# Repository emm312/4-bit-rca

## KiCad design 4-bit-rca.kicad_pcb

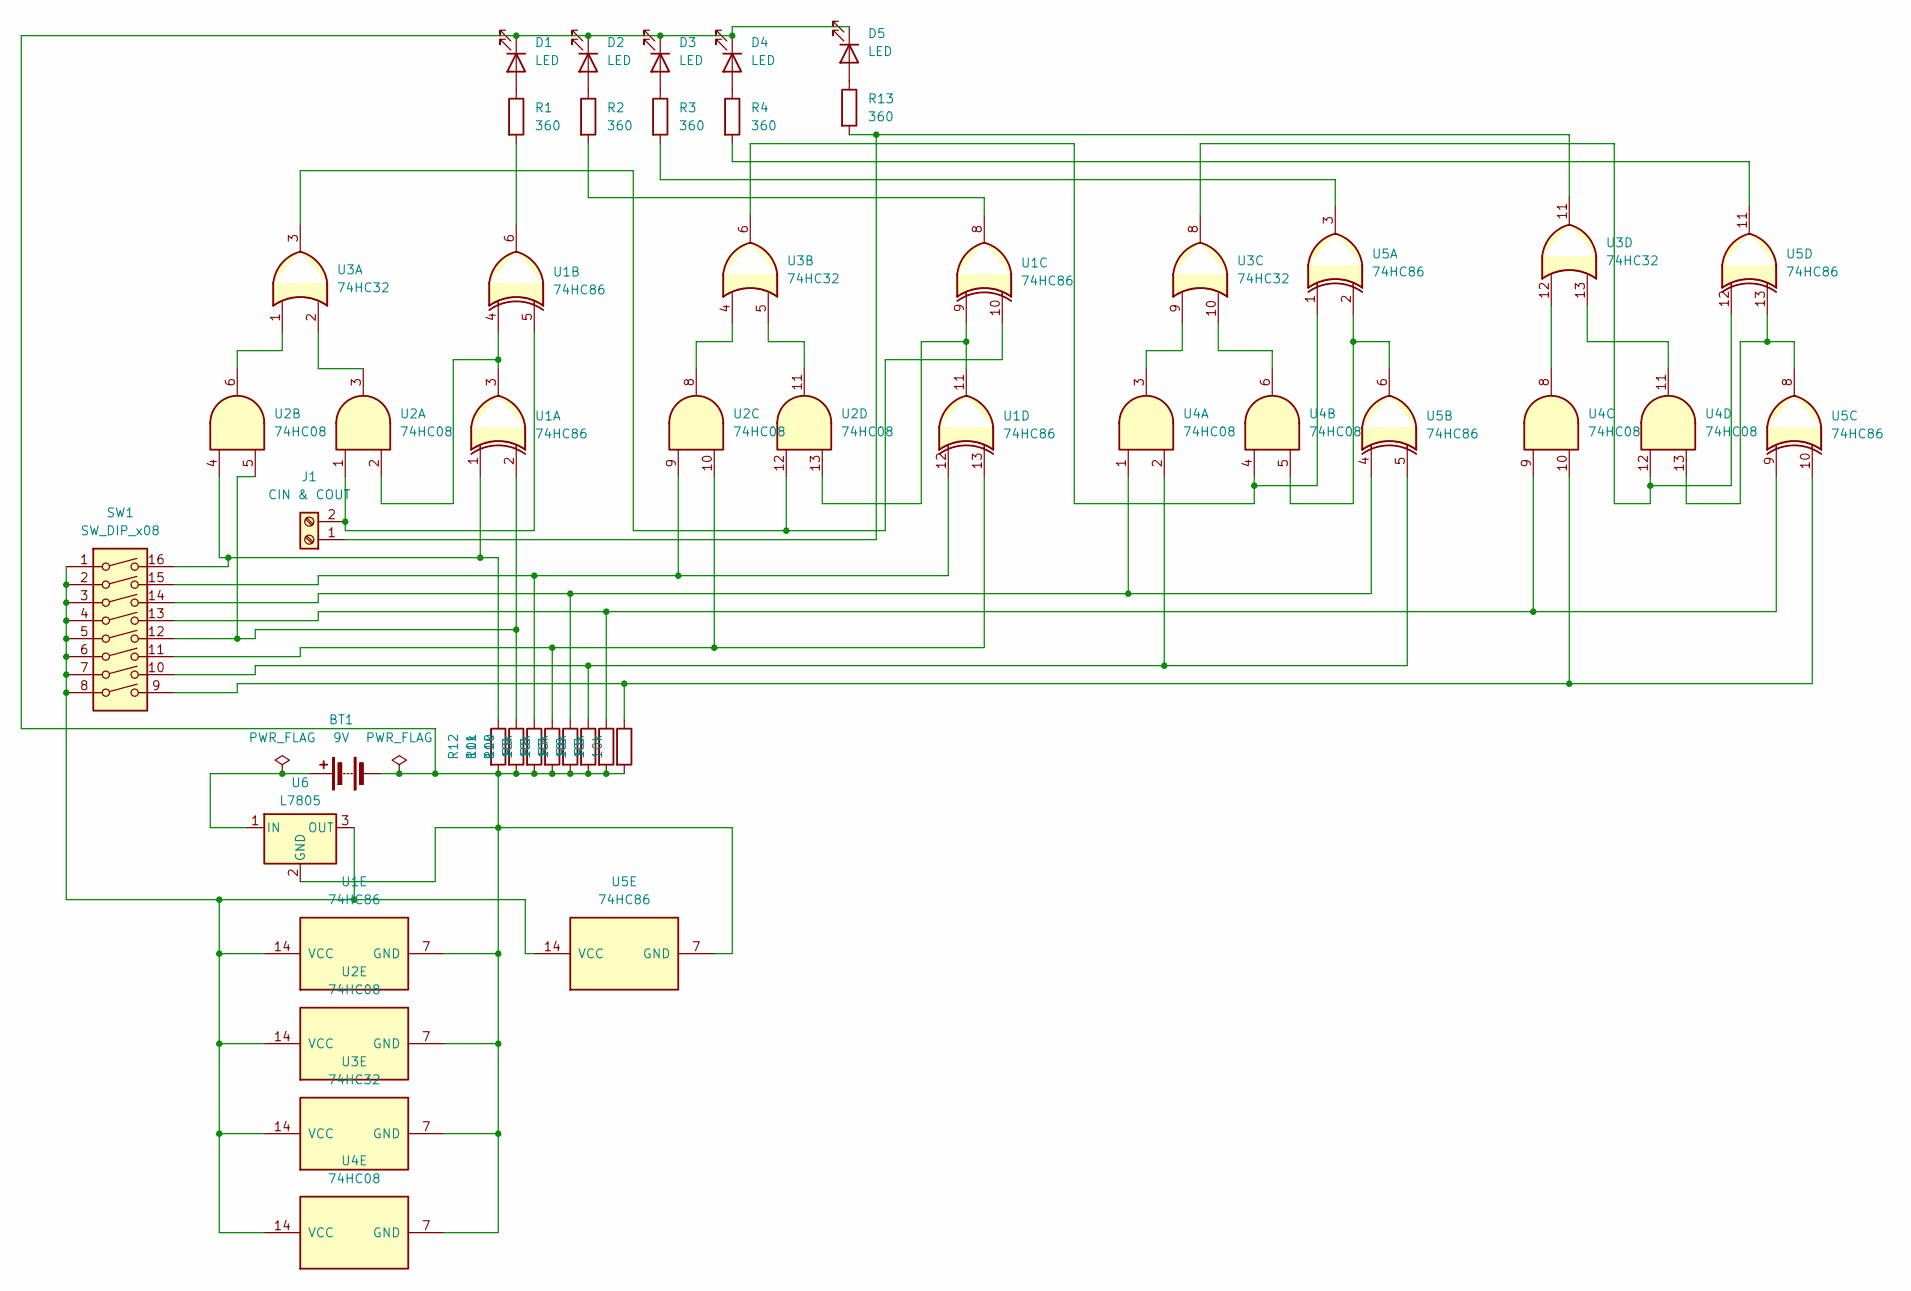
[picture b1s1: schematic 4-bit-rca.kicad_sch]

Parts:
BT1: 9V; PinHeader_1x02_P2.54mm_Vertical
D1, D2, D3, D4, D5: LED; LED_D5.0mm
J1: CIN & COUT; PinHeader_1x02_P2.54mm_Vertical
R1, R2, R3, R4, R13: 360; R_Axial_DIN0207_L6.3mm_D2.5mm_P10.16mm_Horizontal
R5, R6, R7, R8, R9, R10, R11, R12: 10k; R_Axial_DIN0207_L6.3mm_D2.5mm_P10.16mm_Horizontal
SW1: SW_DIP_x08; SW_DIP_SPSTx08_Slide_6.7x21.88mm_W7.62mm_P2.54mm_LowProfile
U1, U5: 74HC86; DIP-14_W7.62mm_Socket_LongPads
U2, U4: 74HC08; DIP-14_W7.62mm_Socket_LongPads
U3: 74HC32; DIP-14_W7.62mm_Socket_LongPads
U6: L7805; TO-220-3_Vertical

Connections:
unnamed: BT1.1 (+), U6.1 (IN)
unnamed: BT1.2 (-), D1.1 (K), D2.1 (K), D3.1 (K), D4.1 (K), D5.1 (K), R5.2, R6.2, R7.2, R8.2, R9.2, R10.2, R11.2, R12.2, U1.7 (GND), U2.7 (GND), U3.7 (GND), U4.7 (GND), U5.7 (GND), U6.2 (GND)
unnamed: D1.2 (A), R1.1
unnamed: D2.2 (A), R2.1
unnamed: D3.2 (A), R3.1
unnamed: D4.2 (A), R4.1
unnamed: D5.2 (A), R13.1
unnamed: J1.1, R13.2, U3.11
unnamed: J1.2, U1.5, U2.1
unnamed: R1.2, U1.6
unnamed: R2.2, U1.8
unnamed: R3.2, U5.3
unnamed: R4.2, U5.11
unnamed: R5.1, SW1.9, U4.10, U5.10
unnamed: R6.1, SW1.13, U4.9, U5.9
unnamed: R7.1, SW1.10, U4.2, U5.5
unnamed: R8.1, SW1.14, U4.1, U5.4
unnamed: R9.1, SW1.11, U1.13, U2.10
unnamed: R10.1, SW1.15, U1.12, U2.9
unnamed: R11.1, SW1.12, U1.2, U2.5
unnamed: R12.1, SW1.16, U1.1, U2.4
unnamed: U1.3, U1.4, U2.2
unnamed: U1.10, U2.12, U3.3
unnamed: U1.9, U1.11, U2.13
unnamed: SW1.1, SW1.2, SW1.3, SW1.4, SW1.5, SW1.6, SW1.7, SW1.8, U1.14 (VCC), U2.14 (VCC), U3.14 (VCC), U4.14 (VCC), U5.14 (VCC), U6.3 (OUT)
unnamed: U2.3, U3.2
unnamed: U2.6, U3.1
unnamed: U2.8, U3.4
unnamed: U2.11, U3.5
unnamed: U3.6, U4.4, U5.1
unnamed: U3.8, U4.12, U5.12
unnamed: U3.9, U4.3
unnamed: U3.10, U4.6
unnamed: U3.12, U4.8
unnamed: U3.13, U4.11
unnamed: U4.5, U5.2, U5.6
unnamed: U4.13, U5.8, U5.13

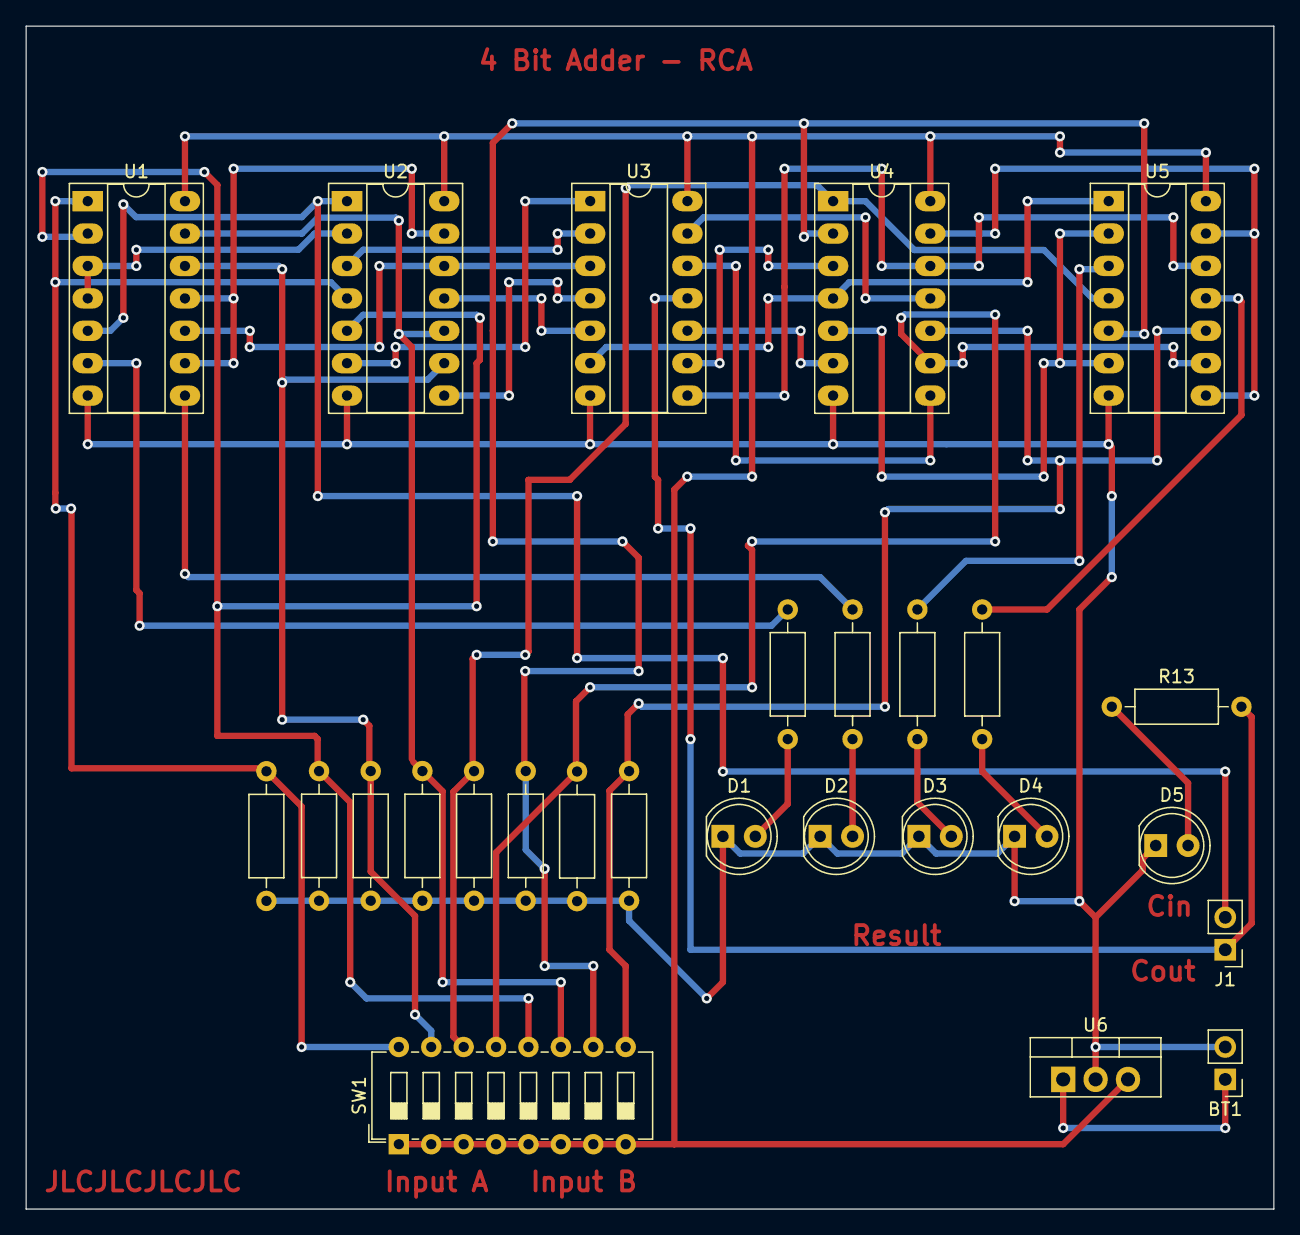
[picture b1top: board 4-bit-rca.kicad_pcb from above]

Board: 2 copper layers, 97.8 x 92.7 mm, 27 parts (0 on the bottom side), 37 nets.

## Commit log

2023-12-29 redo
2023-12-29 aoisjdojoasd
